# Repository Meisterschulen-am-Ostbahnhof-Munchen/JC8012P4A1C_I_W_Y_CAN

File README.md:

# JC8012P4A1C Enclosure & CAN Addon System

Enclosure, mounting and CAN/Power addon board for the Guition JC8012P4A1C (ESP32-P4, 10.1")
display, used by [espVT](https://github.com/Meisterschulen-am-Ostbahnhof-Munchen/espVT).

The system integrates an ISOBUS/CAN interface, 12 V power supply, a 3D-printed enclosure frame,
and an FR4 backplate with VESA 100 mount and speaker. An optional second variant extends the unit
with a 12-key tactile keypad next to the display.

**Online:** interactive BOMs, schematics and drawings at
<https://meisterschulen-am-ostbahnhof-munchen.github.io/JC8012P4A1C_I_W_Y_CAN/>

More renderings and how they are made: [assembly/render/](assembly/render/README.md).

## Repository Structure

The project is structured into PCBs, mechanics and final assembly:

```text
JC8012P4A1C_I_W_Y_CAN/
├── pcbs/
│   ├── can_power/        # CAN-Bus & 12V/5V power supply addon board
│   ├── backplate/        # FR4 backplate with VESA 100 mount & speaker grille (variant 1)
│   ├── backplate_keypad/ # Widened FR4 backplate for variant 2 (with keypad)
│   ├── keypad/           # 12-key tactile keypad PCB (variant 2)
│   ├── keypad_2b/        # keypad with dimmable WL-ICLED backlight (variant 2b)
│   └── can_power_2b/     # CAN board with J4 for the keypad LEDs (variant 2b)
├── mechanics/            # 3D printed frame designs (FreeCAD scripts, STL & STEP files)
├── assembly/             # Assembly drawings (A3 PDF), 3D render models & assembly scripts
├── assembly_bom.csv      # Complete mechanical parts, fasteners & cables BOM
├── mouser_order.csv      # Ordering list for non-Würth components
└── README.md
```

## Variants

| Component | Variant 1 (Standard) | Variant 2 (with Keypad) | Variant 2b (backlit keypad) |
|---|---|---|---|
| Display | Guition JC8012P4A1C (10.1" ESP32-P4) | Guition JC8012P4A1C (10.1" ESP32-P4) | as variant 2 |
| CAN / Power Board | [`pcbs/can_power/`](pcbs/can_power/README.md) | [`pcbs/can_power/`](pcbs/can_power/README.md) | [`pcbs/can_power_2b/`](pcbs/can_power_2b/README.md) (with J4 for the LEDs) |
| Frame | `mechanics/frame.stl` | `mechanics/frame_keypad.stl` | as variant 2 |
| Backplate | [`pcbs/backplate/`](pcbs/backplate/README.md) | [`pcbs/backplate_keypad/`](pcbs/backplate_keypad/README.md) (296.9 mm wide) | as variant 2 |
| Keypad | — | [`pcbs/keypad/`](pcbs/keypad/README.md) (12 tactile keys F1–F12) | [`pcbs/keypad_2b/`](pcbs/keypad_2b/README.md) (WL-ICLED windows + background, dimmable) |
| Assembly Drawing | [assembly/JC8012P4A1C_assembly_variant1.pdf](assembly/JC8012P4A1C_assembly_variant1.pdf) | [assembly/JC8012P4A1C_assembly_variant2_keypad.pdf](assembly/JC8012P4A1C_assembly_variant2_keypad.pdf) | as variant 2, plus the 3 wire LED cable |

Details on mechanics: [mechanics/README.md](mechanics/README.md).  
Details on assembly: [assembly/README.md](assembly/README.md).

## Bills of Materials (BOM)

| BOM | File |
|---|---|
| CAN & Power board | [pcbs/can_power/production/JC8012P4A1C_I_W_Y_CAN_bom.csv](pcbs/can_power/production/JC8012P4A1C_I_W_Y_CAN_bom.csv) |
| Back plate (variant 1) | [pcbs/backplate/production/JC8012P4A1C_backplate_bom.csv](pcbs/backplate/production/JC8012P4A1C_backplate_bom.csv) |
| Back plate (variant 2, keypad) | [pcbs/backplate_keypad/production/JC8012P4A1C_backplate_keypad_bom.csv](pcbs/backplate_keypad/production/JC8012P4A1C_backplate_keypad_bom.csv) |
| Keypad (variant 2) | [pcbs/keypad/production/JC8012P4A1C_keypad_bom.csv](pcbs/keypad/production/JC8012P4A1C_keypad_bom.csv) |
| Keypad (variant 2b, backlit) | [pcbs/keypad_2b/production/JC8012P4A1C_keypad_2b_bom.csv](pcbs/keypad_2b/production/JC8012P4A1C_keypad_2b_bom.csv) |
| CAN & Power board (variant 2b) | [pcbs/can_power_2b/production/JC8012P4A1C_I_W_Y_CAN_2b_bom.csv](pcbs/can_power_2b/production/JC8012P4A1C_I_W_Y_CAN_2b_bom.csv) |
| Final assembly (mechanical fasteners, cables) | [assembly_bom.csv](assembly_bom.csv) |
| Parts to order at Mouser (all non-Würth parts) | [mouser_order.csv](mouser_order.csv) |

### Interactive HTML BOMs (Assembly Checklists)

For manual assembly, interactive HTML BOMs (with checkboxes for soldering and inspection) are provided:

| Board | Interactive BOM |
|---|---|
| CAN & Power board | [pcbs/can_power/production/JC8012P4A1C_I_W_Y_CAN_ibom.html](pcbs/can_power/production/JC8012P4A1C_I_W_Y_CAN_ibom.html) |
| Back plate | [pcbs/backplate/production/JC8012P4A1C_backplate_ibom.html](pcbs/backplate/production/JC8012P4A1C_backplate_ibom.html) |
| Back plate (keypad variant) | [pcbs/backplate_keypad/production/JC8012P4A1C_backplate_keypad_ibom.html](pcbs/backplate_keypad/production/JC8012P4A1C_backplate_keypad_ibom.html) |
| Keypad | [pcbs/keypad/production/JC8012P4A1C_keypad_ibom.html](pcbs/keypad/production/JC8012P4A1C_keypad_ibom.html) |
| Keypad 2b | [pcbs/keypad_2b/production/JC8012P4A1C_keypad_2b_ibom.html](pcbs/keypad_2b/production/JC8012P4A1C_keypad_2b_ibom.html) |
| CAN & Power board 2b | [pcbs/can_power_2b/production/JC8012P4A1C_I_W_Y_CAN_2b_ibom.html](pcbs/can_power_2b/production/JC8012P4A1C_I_W_Y_CAN_2b_ibom.html) |

## Manufacturing

Each PCB folder in `pcbs/` contains its complete KiCad 10 project, local component libraries (`lib/`), documentation (`docs/`), and fabrication outputs (`production/`).
See the respective README files in [`pcbs/can_power/`](pcbs/can_power/README.md), [`pcbs/backplate/`](pcbs/backplate/README.md), [`pcbs/backplate_keypad/`](pcbs/backplate_keypad/README.md), and [`pcbs/keypad/`](pcbs/keypad/README.md) for generation commands and specifications.

The 3D-printable frame is generated using FreeCAD scripts in [`mechanics/`](mechanics/README.md).

## Licence

- Schematics, PCB layouts, scripts and documentation: GPL-3.0 ([LICENSE](LICENSE)).
- `pcbs/*/lib/` and `assembly/models/`: symbols, footprints and 3D models from the Würth Elektronik eiSos libraries, licensed CC BY-SA 4.0 with the Würth exception for designs that use them (see `Wurth_Disclaimer_READ_ME.txt` in these folders).
- Footprints and 3D models from the KiCad standard libraries: CC BY-SA 4.0 with the KiCad exception.
- `mechanics/`: derivative of a Thingiverse design by 8bitmcu, CC BY-SA, see [mechanics/LICENSE.md](mechanics/LICENSE.md).

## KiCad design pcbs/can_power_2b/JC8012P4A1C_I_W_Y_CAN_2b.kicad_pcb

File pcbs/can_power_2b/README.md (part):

# JC8012P4A1C CAN & Power Board, variant 2b

The CAN board of `../can_power` with one addition for the backlit keypad
`../keypad_2b`: **J4** brings 5 V, GND and the LED data (GPIO2) to the keypad.
Everything else is unchanged.

ISOBUS / CAN interface (250 kbit/s) for the Guition JC8012P4A1C (ESP32-P4, 10.1")
display, used by [espVT](https://github.com/Meisterschulen-am-Ostbahnhof-Munchen/espVT).
The board is mounted on the back of the display board and powered from the 12 V
board net. It also supplies 5 V to the display board.

KiCad 10 project. Project-local libraries are in `lib/`.

Top view: [docs/board_3d_top.png](docs/board_3d_top.png)

## Connections

| Connector | Part | Purpose |
|---|---|---|
| J1 | Würth WR-PHD 610110249121 (2×5 pin header, SMT, right angled) | ribbon cable to IDC D-Sub 9 female Würth 618009221923 |
| J2 | Würth WR-FPC 68711414522 (14 pin, 0.5 mm) | FFC to FPC3 "EXTEND1" of the display board |
| J3 | Würth WR-WTB 653104131822 (4 pin, 1.25 mm) | 5 V to CN2 of the display board |
| J4 | Würth WR-WTB 653103131822 (3 pin, 1.25 mm) | 5 V, GND and LED data to J2 of the keypad 2b |

### D-Sub 9 (via ribbon cable on J1)

Pinout of the Müller-Elektronik BASIC-Terminal CAN-ISO connector. It fits the
adapter cable 481595 (D-Sub 9 male to In-Cab CPC-9 female).

| D-Sub | J1 | Signal |
|---|---|---|
| 1 | 1 | CAN_L |
| 2 | 3 | CAN_L |
| 3 | 5 | TBC_GND (see R8) |
| 4 | 7 | CAN_H |
| 5 | 9 | TBC_PWR_in (not used) |
| 6 | 2 | ECU_GND |
| 7 | 4 | CAN_H |
| 8 | 6 | TBC_PWR_out |
| 9 | 8 | ECU_PWR (12 V board net) |
| – | 10 | not used |

CAN_L (1/2) and CAN_H (4/7) are connected on the board to loop the bus through.

**Pin numbering:** J1 is numbered like the IDC socket 61201023021: pin 1 and
all odd pins are in the upper row (away from the PCB, pin tips away from the
body of J1), the even pins in the lower row. Pin 1 is at the end next to R8
(silkscreen line next to the pad). The Würth datasheet of 610110249121 numbers
the two rows the other way round (pin 1 in the lower row); with that numbering
every position of the IDC socket meets the neighbour pin of the other row
(1↔2, 3↔4, ...). The footprint therefore deviates from the datasheet on
purpose (since Rev B).

**Polarisation:** J1 has no shroud (an 8 mm high part is the maximum under
the cover, a box header with IDC socket would be too high). To prevent the
IDC socket from being plugged in turned by 180°, cut off pin 10 of J1 (lower
row, end away from R8, marked "cut" on the silkscreen) and close position 10
of the IDC socket with a coding plug. Pins 9 and 10 are not used. Plugged in
turned, ECU_PWR (12 V) would end up on CAN_L and the board GND would stay
open.

## Mechanics

- All parts on the top side (SMT only), nothing on the bottom side
- Stack height: cover 14 mm − display board 1.5 mm − M2 standoffs 3 mm −
  addon board 1.5 mm ≈ 8 mm free above the addon board
- Fixing on the 58 × 46 mm grid of the display board standoffs S1–S4
  (H1 = S1, H2 = S4, H3 = S2, H4 = S3): SMD steel spacers Würth WA-SMST
  9774025943R (L 2.5 mm, through hole 2.25 mm), land pattern from the
  datasheet, but the GND pad on top is a copper ring 3.5-5.3 mm: 0.25 mm without
  copper around the 3.0 mm **non-plated** hole for the Ø 2.8 × 1.4 mm collar of
  the spacer, so the hole is clearly unplated in the JLC order.
- Screws **M2×6**, without washer: spacer 2.5 mm + PCB 1.6 mm leaves 1.9 mm
  thread engagement in the 2.5 mm deep blind thread of S1–S4. M2×8 would
  bottom out.
- Notches for CN5 (pin header), the 100 µF capacitor next to S4 and the
  CR1220 RTC holder of the display board

### FPC3 (J2)

| Pin | Signal |
|---|---|
| 1, 2 | GND |
| 7 | CAN_RXD (GPIO5) |
| 8 | CAN_TXD (GPIO4) |
| 9 | CAN_NEN (GPIO3, 10k pull-down: transceiver active by default) |
| 10 | LED_DATA (GPIO2) -> R11 33 R -> J4 pin 3 |
| 13, 14 | +3V3 (VDDA, transceiver VIO) |

FFC: 14 pin, 0.5 mm pitch, **type B (contacts on opposite sides)**.
The cable leaves FPC3 towards the board edge, makes one 180° turn and enters
J2 from the edge of the addon board. Both connectors are bottom-contact ZIF
with the same orientation (opening towards the edge, pin 1 on the right
side seen from the back of the display, next to the TF card), so pin 1
connects to pin 1. A type A cable would have its contacts facing up at J2;
turning it over to make it fit reverses the pin order and swaps GND (1/2)
and 3V3 (13/14).

## Keypad backlight (J4)

| J4 | Signal |
|---|---|
| 1 | +5V (In2 plane) |
| 2 | GND |
| 3 | LED data: GPIO2 (FPC3 pin 10) through R11 33 R |

J4 sits at the bottom notch of the board, the opening points into the notch.
GPIO2 is in the 3.3 V domain (VDDPST_1). GPIO45-48 on FPC3 were not used: they are
supplied from ESP_LDO_VO4 like the SD card and can be switched to 1.8 V.
The level shifter to 5 V is on the keypad. Six GND stitching vias under J4 / R11
were removed, the board text was moved up and reads "Rev 2b".

## Termination

ISO 11783-2 ECU Type I WEAK: split termination 750 Ω + 750 Ω with 47 nF to GND.

## TBC power output and R8

Like the BASIC-Terminal, the board supplies power for the terminating bias
circuits (TBC) on D-Sub pin 8 (TBC_PWR_out): board net minus about 0.4 V
(Schottky diode D4), limited by PTC F2 (0.14 A). Some harnesses do not start
without it.

**R8 (0 Ω, TBC_GND to GND) is not fitted (DNP) by default.** This keeps
TBC_GND isolated, which is the compatible default. If a harness needs a
TBC_GND return for its terminator, fit R8 with a 0 Ω resistor (0603).

## Power

- 12 V board net only (ECU_PWR), fuse F1 1 A slow
- Bidirectional TVS Würth 824551241 (SMDJ24CA), clamping ≤ 38.9 V
- Reverse polarity protection: dual P-MOSFET Vishay Si4948BEY (SO-8), both
  halves in parallel, 15 V gate zener. Drop-in for the KiCad symbol
  DMP6050SSD (same SO-8 pinout S1 G1 S2 G2 D2 D2 D1 D1), which is used as
  the schematic symbol.
- Buck converter Würth MagI³C 171030601: 5 V / 3 A for the transceiver and the display board

## Test points

SMD pads (1.5 mm), labelled with the net name on the silkscreen:

| TP | Net | Position |
|---|---|---|
| TP1 | +5V | next to J3 |
| TP2 | GND | next to J3 |
| TP3 | CAN_H | between D1 and J1 |
| TP4 | CAN_L | between D1 and J1 |
| TP5 | VIN_PROT (12 V after fuse and reverse polarity protection) | right of C13, below L2 |

## PCB

66 × 54 mm, 1.6 mm, 6 layers:

| Layer | Use |
|---|---|
| F.Cu | all parts and signals, GND pour, local pours for VIN_PROT, VIN_BUCK and +5V |
| In1.Cu | GND plane |
| In2.Cu | +5V plane |
| In3.Cu | GND plane (also balances the copper of In2) |
| In4.Cu | GND plane |
| B.Cu | GND plane, one short signal (CAN_NEN) |

- Vias 0.5 mm / 0.3 mm drill (a 0.2 mm drill costs extra at JLCPCB). Many vias are placed in SMD pads (GND and
  +5V pads, 77 thermal vias under the exposed pad of U2), so the vias
  **must be epoxy filled and capped** (via-in-pad). Without this, solder
  is drawn into the holes during reflow.
- GND stitching vias on a 4 mm grid connect all GND layers.
- Pours connect solid to SMD pads and to the spacer pads H1–H4 (reflow
  soldering, a hand soldering iron will not heat them).
- Net classes: Power 0.8 mm (12 V path and +5V), CAN 0.3 mm, Default 0.25 mm.

## Manufacturing

The current Gerber and drill files are in the zip
`production/JC8012P4A1C_I_W_Y_CAN_2b_gerber.zip` (ready for upload), the BOM
in `production/JC8012P4A1C_I_W_Y_CAN_2b_bom.csv`. Make them again after changes
to the board: in KiCad PCB editor → File → Fabrication Outputs → Gerbers and
Drill Files, or from the command line:

```sh
kicad-cli pcb export gerbers -o production/gerber -l F.Cu,In1.Cu,In2.Cu,In3.Cu,In4.Cu,B.Cu,F.Paste,B.Paste,F.Silkscreen,B.Silkscreen,F.Mask,B.Mask,Edge.Cuts --subtract-soldermask --no-x2 --no-netlist --check-zones JC8012P4A1C_I_W_Y_CAN_2b.kicad_pcb
kicad-cli pcb export drill -o production/gerber/ --format excellon --excellon-units mm --excellon-separate-th JC8012P4A1C_I_W_Y_CAN_2b.kicad_pcb
```

Zip the content of `production/gerber` (the folder itself is not in the
repository) to `production/JC8012P4A1C_I_W_Y_CAN_2b_gerber.zip` and upload it (e.g. JLCPCB:
6 layers, 1.6 mm, via covering "Epoxy Filled & Capped").

Interactive HTML BOM:

```sh
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
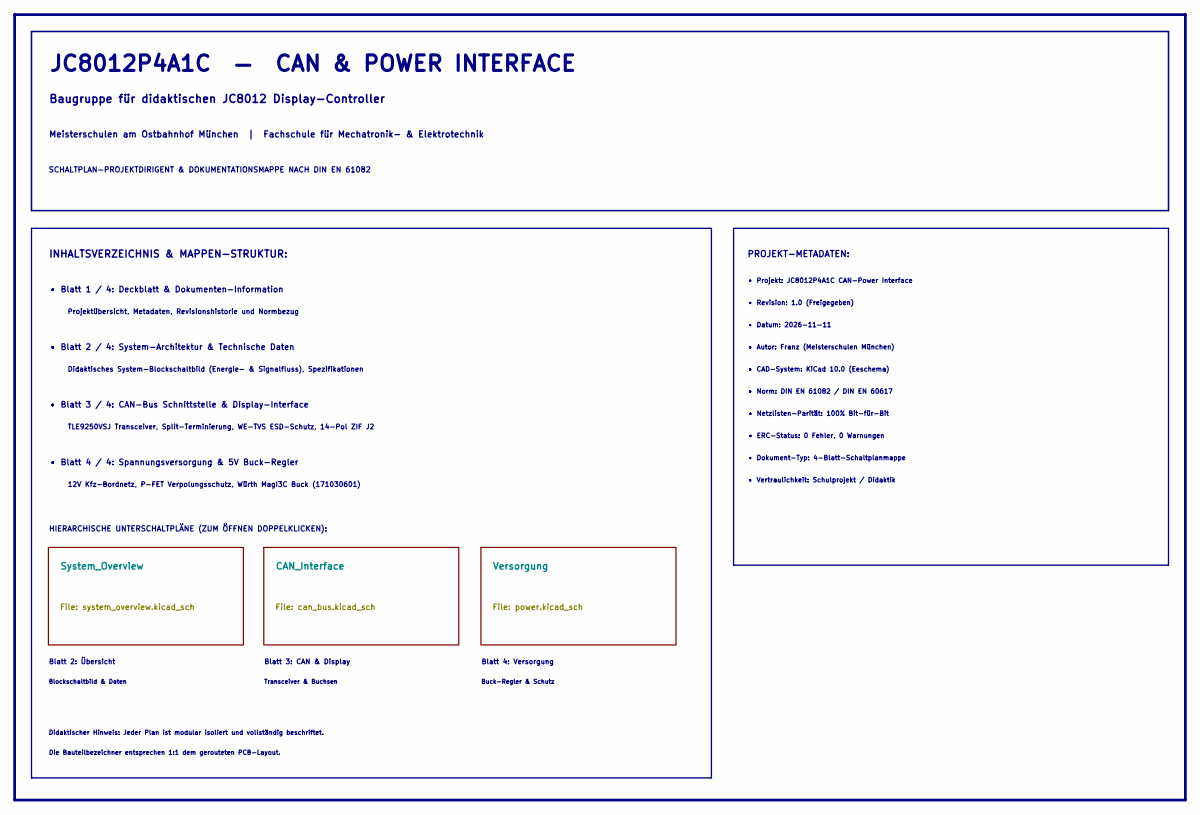
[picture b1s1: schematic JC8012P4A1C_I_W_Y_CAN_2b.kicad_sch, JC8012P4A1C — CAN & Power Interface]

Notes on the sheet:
Projektübersicht, Metadaten, Revisionshistorie und Normbezug
12V Kfz-Bordnetz, P-FET Verpolungsschutz, Würth MagI3C Buck (171030601)
Blatt 2: Übersicht
• CAD-System: KiCad 10.0 (Eeschema)
• Revision: 1.0 (Freigegeben)
HIERARCHISCHE UNTERSCHALTPLÄNE (ZUM ÖFFNEN DOPPELKLICKEN):
Didaktisches System-Blockschaltbild (Energie- & Signalfluss), Spezifikationen
• Netzlisten-Parität: 100% Bit-für-Bit
PROJEKT-METADATEN:
Meisterschulen am Ostbahnhof München | Fachschule für Mechatronik- & Elektrotechnik
• Norm: DIN EN 61082 / DIN EN 60617
• Blatt 3 / 4: CAN-Bus Schnittstelle & Display-Interface
Baugruppe für didaktischen JC8012 Display-Controller
• Dokument-Typ: 4-Blatt-Schaltplanmappe
• ERC-Status: 0 Fehler, 0 Warnungen
Blatt 4: Versorgung
INHALTSVERZEICHNIS & MAPPEN-STRUKTUR:
• Blatt 4 / 4: Spannungsversorgung & 5V Buck-Regler
Buck-Regler & Schutz
• Blatt 2 / 4: System-Architektur & Technische Daten
Blatt 3: CAN & Display
Blockschaltbild & Daten
SCHALTPLAN-PROJEKTDIRIGENT & DOKUMENTATIONSMAPPE NACH DIN EN 61082
• Datum: 2026-11-11
• Vertraulichkeit: Schulprojekt / Didaktik
JC8012P4A1C — CAN & POWER INTERFACE
• Blatt 1 / 4: Deckblatt & Dokumenten-Information
Die Bauteilbezeichner entsprechen 1:1 dem gerouteten PCB-Layout.
Transceiver & Buchsen
TLE9250VSJ Transceiver, Split-Terminierung, WE-TVS ESD-Schutz, 14-Pol ZIF J2
Didaktischer Hinweis: Jeder Plan ist modular isoliert und vollständig beschriftet.
• Autor: Franz (Meisterschulen München)
• Projekt: JC8012P4A1C CAN-Power Interface

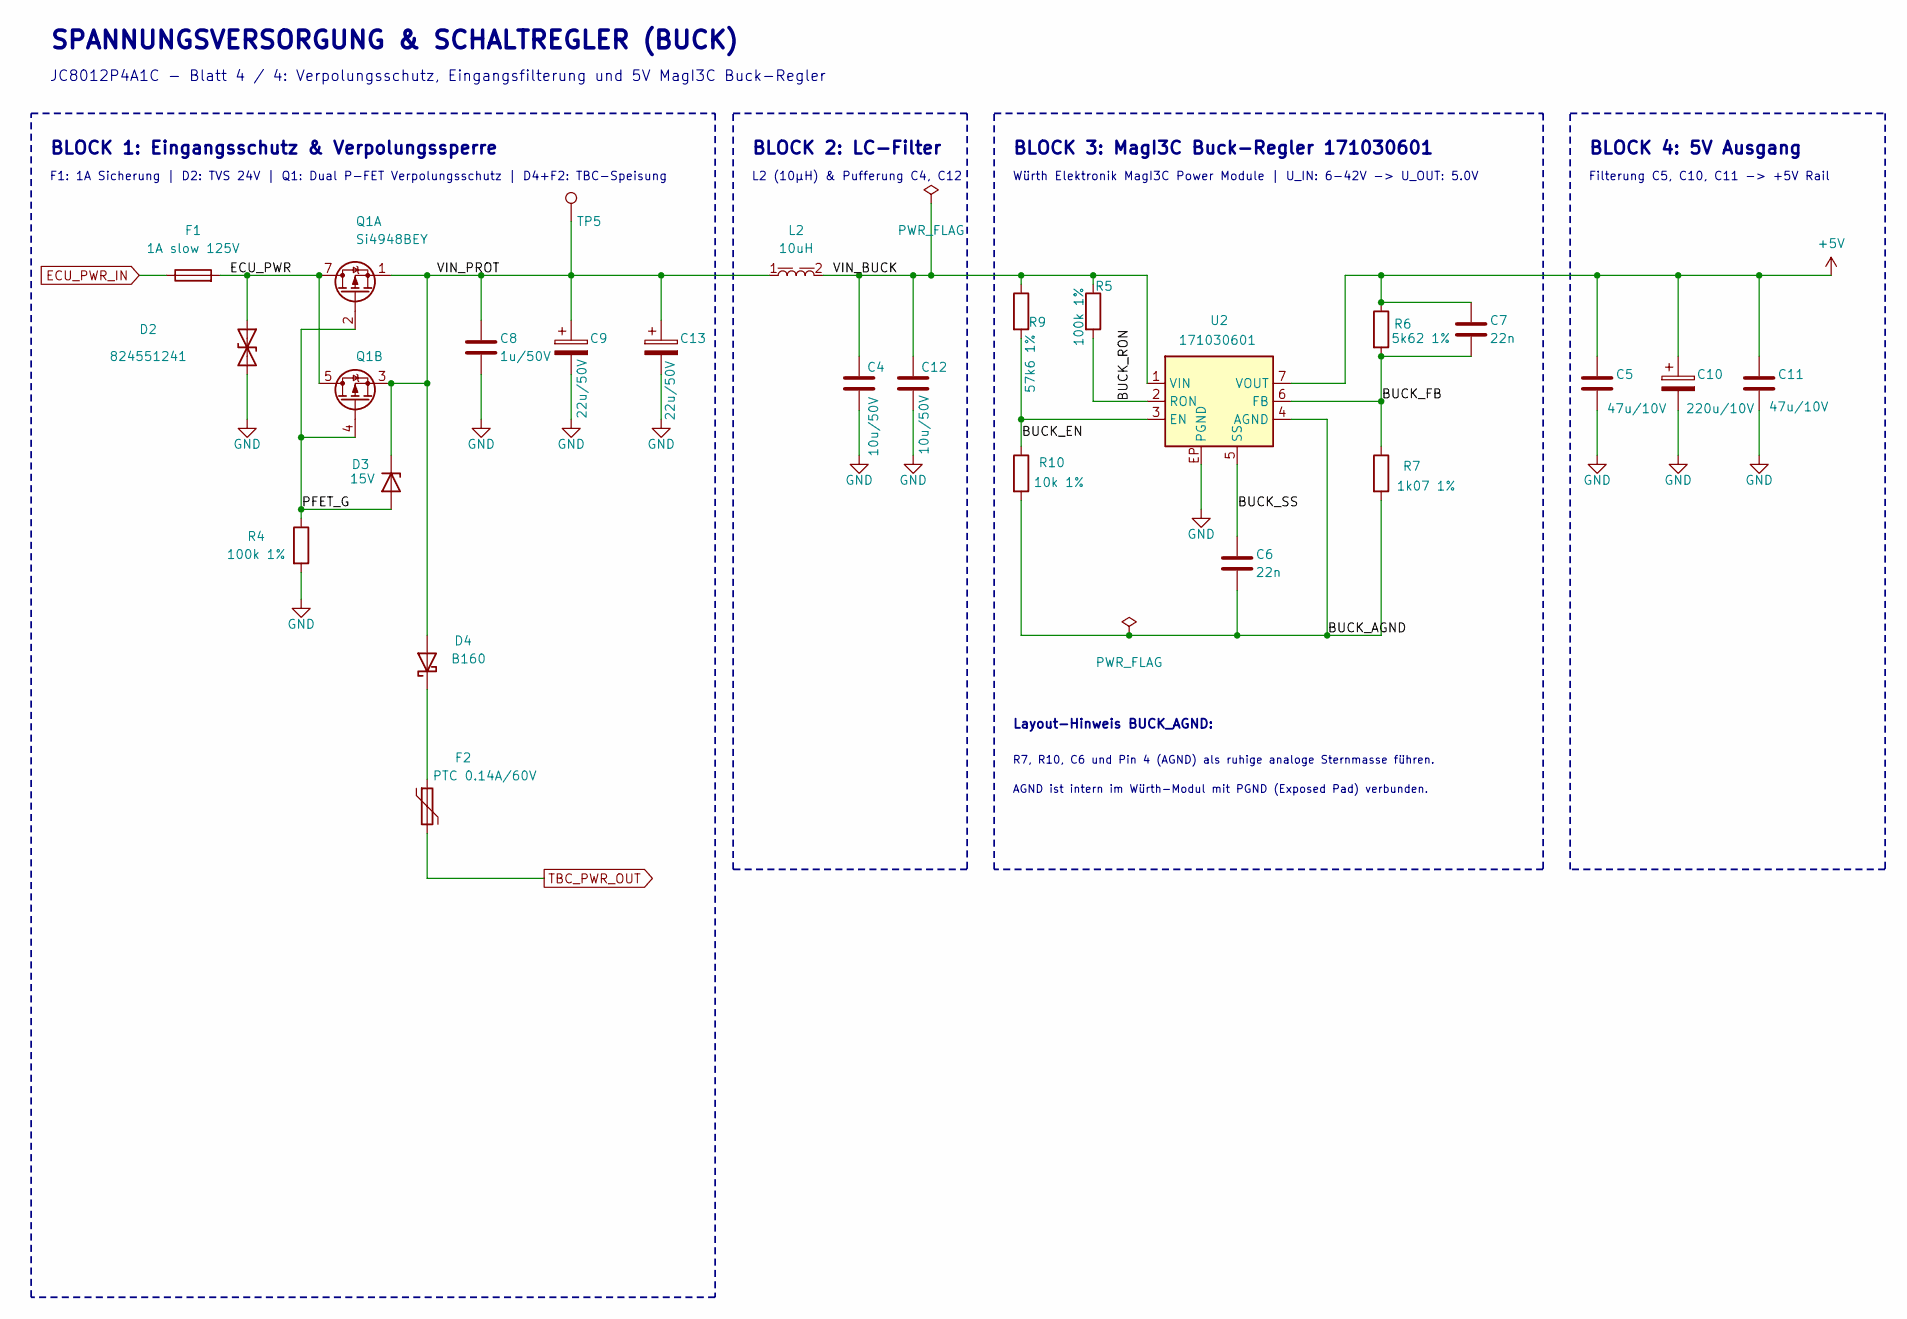
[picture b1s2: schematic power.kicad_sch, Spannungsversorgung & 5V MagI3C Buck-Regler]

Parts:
C4, C12: 10u/50V; C_1210_3225Metric; MPN 885012209073
C5, C11: 47u/10V; C_1210_3225Metric; MPN 885012109007
C6, C7: 22n; C_0603_1608Metric; MPN 885012206091
C8: 1u/50V; C_1210_3225Metric; MPN 885012209047
C9, C13: 22u/50V; CP_Wurth_WCAP-ASLI-D6.3L5.5; MPN 865080643008
C10: 220u/10V; CP_Wurth_WCAP-PSLP-D6.3L5.8; MPN 875105244013
D2: 824551241; D_Wurth_WE-TVSP-DO214-AB-3000W_BI; MPN 824551241
D3: 15V; D_SOD-123; MPN MMSZ5245B_R1_00001
D4: B160; D_SMA; MPN B160-13-F
F1: 1A slow 125V; Fuse_Littelfuse-NANO2-451_453; MPN 0452001.MRL
F2: PTC 0.14A/60V; Fuse_1812_4532Metric; MPN MF-MSMF014-2
L2: 10uH; L_Wurth_WE-PD2-5848; MPN 74477410
Q1: Si4948BEY; SOIC-8_3.9x4.9mm_P1.27mm; MPN SI4948BEY-T1-E3
R4, R5: 100k 1%; R_0603_1608Metric; MPN RC0603FR-07100KL
R6: 5k62 1%; R_0603_1608Metric; MPN RC0603FR-075K62L
R7: 1k07 1%; R_0603_1608Metric; MPN RC0603FR-071K07L
R9: 57k6 1%; R_0603_1608Metric; MPN RC0603FR-0757K6L
R10: 10k 1%; R_0603_1608Metric; MPN RC0603FR-0710KL
TP5: VIN_PROT; TestPoint_Pad_D1.5mm
U2: 171030601; U_Wurth_WPME-VDRM-TO263-7EP; MPN 171030601

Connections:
+5V: C5.1, C7.1, C10.1, C11.1, R6.1, U2.7 (VOUT); also elsewhere on the board
/Versorgung/BUCK_AGND: C6.2, R7.2, R10.2, U2.4 (AGND)
/Versorgung/BUCK_EN: R9.2, R10.1, U2.3 (EN)
/Versorgung/BUCK_FB: C7.2, R6.2, R7.1, U2.6 (FB)
/Versorgung/BUCK_RON: R5.2, U2.2 (RON)
/Versorgung/BUCK_SS: C6.1, U2.5 (SS)
/Versorgung/ECU_PWR: D2.1 (A1), F1.2, Q1.5 (D2), Q1.6 (D2), Q1.7 (D1), Q1.8 (D1)
/Versorgung/PFET_G: D3.2 (A), Q1.2 (G1), Q1.4 (G2), R4.1
/Versorgung/VIN_BUCK: C4.1, C12.1, L2.2, R5.1, R9.1, U2.1 (VIN)
/Versorgung/VIN_PROT: C8.1, C9.1, C13.1, D3.1 (K), D4.2 (A), L2.1, Q1.1 (S1), Q1.3 (S2), TP5.1 (1_1)
unnamed: D4.1 (K), F2.1
TBC_PWR_OUT: F2.2; also elsewhere on the board

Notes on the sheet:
Würth Elektronik MagI3C Power Module | U_IN: 6-42V -> U_OUT: 5.0V
JC8012P4A1C - Blatt 4 / 4: Verpolungsschutz, Eingangsfilterung und 5V MagI3C Buck-Regler
R7, R10, C6 und Pin 4 (AGND) als ruhige analoge Sternmasse führen.
BLOCK 3: MagI3C Buck-Regler 171030601
BLOCK 4: 5V Ausgang
Layout-Hinweis BUCK_AGND:
AGND ist intern im Würth-Modul mit PGND (Exposed Pad) verbunden.
F1: 1A Sicherung | D2: TVS 24V | Q1: Dual P-FET Verpolungsschutz | D4+F2: TBC-Speisung
BLOCK 1: Eingangsschutz & Verpolungssperre
L2 (10µH) & Pufferung C4, C12
Filterung C5, C10, C11 -> +5V Rail
SPANNUNGSVERSORGUNG & SCHALTREGLER (BUCK)
BLOCK 2: LC-Filter

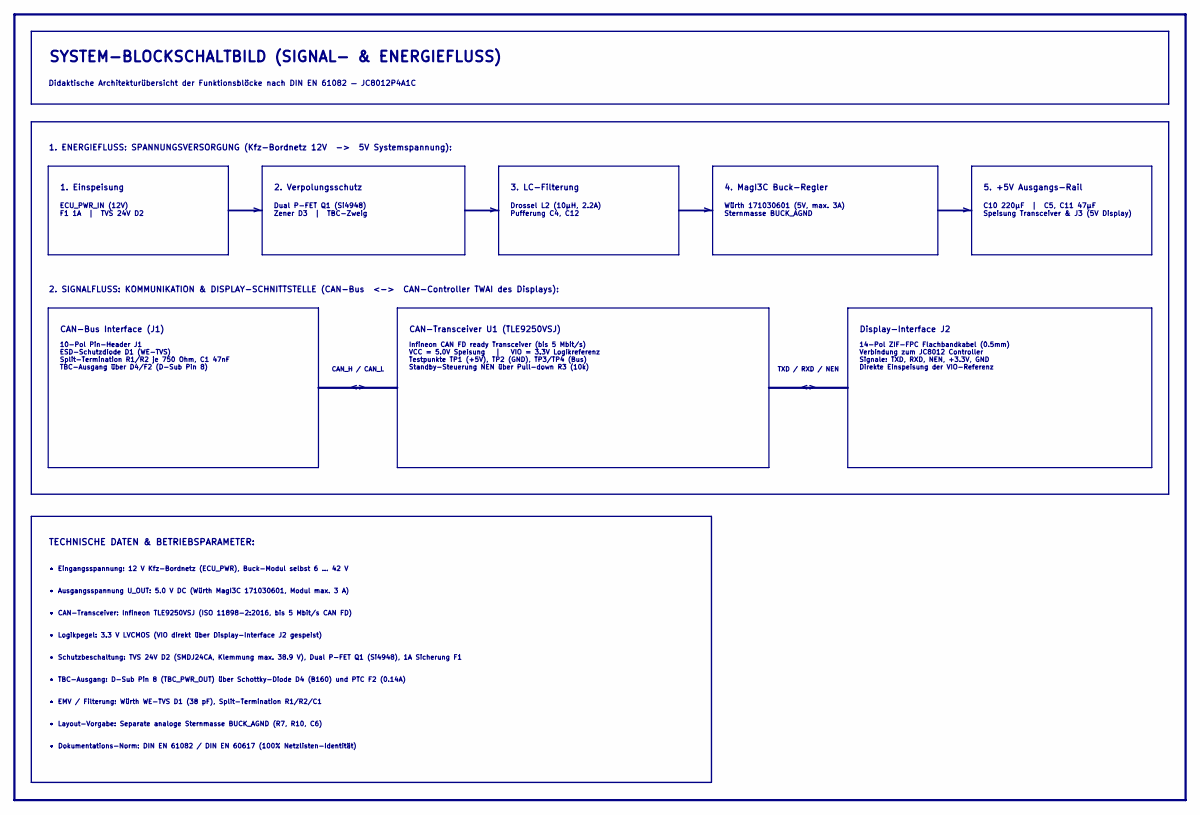
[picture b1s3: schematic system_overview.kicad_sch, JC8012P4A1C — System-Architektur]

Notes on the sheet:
1. Einspeisung
5. +5V Ausgangs-Rail
• Schutzbeschaltung: TVS 24V D2 (SMDJ24CA, Klemmung max. 38.9 V), Dual P-FET Q1 (Si4948), 1A Sicherung F1
TECHNISCHE DATEN & BETRIEBSPARAMETER:
CAN_H / CAN_L
Würth 171030601 (5V, max. 3A) Sternmasse BUCK_AGND
• EMV / Filterung: Würth WE-TVS D1 (38 pF), Split-Termination R1/R2/C1
• Layout-Vorgabe: Separate analoge Sternmasse BUCK_AGND (R7, R10, C6)
• CAN-Transceiver: Infineon TLE9250VSJ (ISO 11898-2:2016, bis 5 Mbit/s CAN FD)
Drossel L2 (10µH, 2.2A) Pufferung C4, C12
Infineon CAN FD ready Transceiver (bis 5 Mbit/s) VCC = 5.0V Speisung | VIO = 3.3V Logikreferenz Testpunkte TP1 (+5V), TP2 (GND), TP3/TP4 (Bus) Standby-Steuerung NEN über Pull-down R3 (10k)
CAN-Transceiver U1 (TLE9250VSJ)
Dual P-FET Q1 (Si4948) Zener D3 | TBC-Zweig
Didaktische Architekturübersicht der Funktionsblöcke nach DIN EN 61082 — JC8012P4A1C
1. ENERGIEFLUSS: SPANNUNGSVERSORGUNG (Kfz-Bordnetz 12V -> 5V Systemspannung):
4. MagI3C Buck-Regler
14-Pol ZIF-FPC Flachbandkabel (0.5mm) Verbindung zum JC8012 Controller Signale: TXD, RXD, NEN, +3.3V, GND Direkte Einspeisung der VIO-Referenz
TXD / RXD / NEN
2. SIGNALFLUSS: KOMMUNIKATION & DISPLAY-SCHNITTSTELLE (CAN-Bus <-> CAN-Controller TWAI des Displays):
3. LC-Filterung
C10 220µF | C5, C11 47µF Speisung Transceiver & J3 (5V Display)
• TBC-Ausgang: D-Sub Pin 8 (TBC_PWR_OUT) über Schottky-Diode D4 (B160) und PTC F2 (0.14A)
• Dokumentations-Norm: DIN EN 61082 / DIN EN 60617 (100% Netzlisten-Identität)
• Logikpegel: 3.3 V LVCMOS (VIO direkt über Display-Interface J2 gespeist)
Display-Interface J2
2. Verpolungsschutz
CAN-Bus Interface (J1)
• Ausgangsspannung U_OUT: 5.0 V DC (Würth MagI3C 171030601, Modul max. 3 A)
ECU_PWR_IN (12V) F1 1A | TVS 24V D2
10-Pol Pin-Header J1 ESD-Schutzdiode D1 (WE-TVS) Split-Termination R1/R2 je 750 Ohm, C1 47nF TBC-Ausgang über D4/F2 (D-Sub Pin 8)
• Eingangsspannung: 12 V Kfz-Bordnetz (ECU_PWR), Buck-Modul selbst 6 ... 42 V
SYSTEM-BLOCKSCHALTBILD (SIGNAL- & ENERGIEFLUSS)

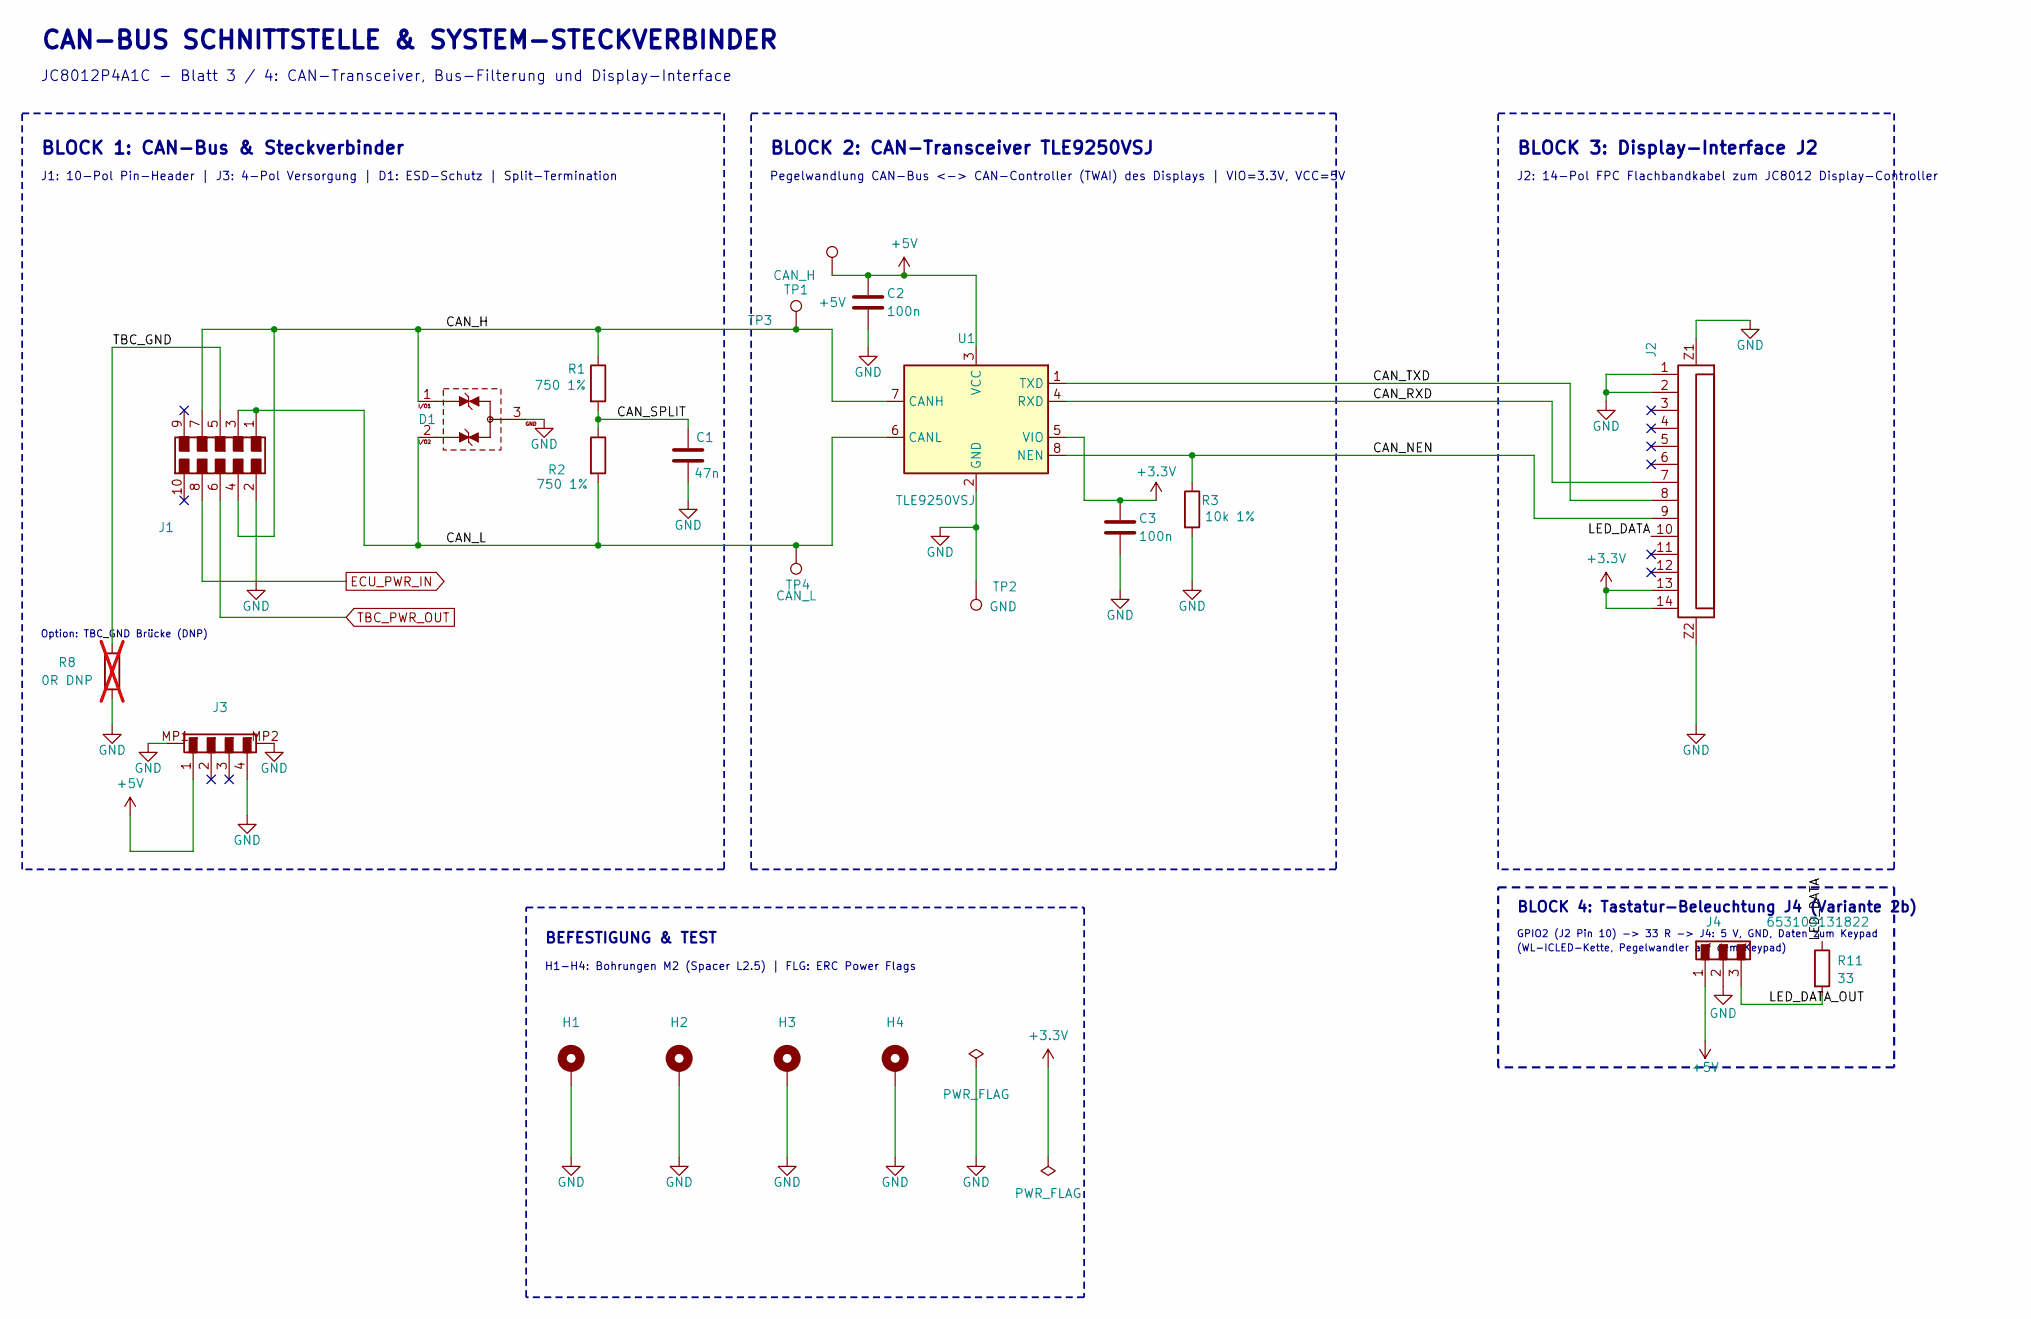
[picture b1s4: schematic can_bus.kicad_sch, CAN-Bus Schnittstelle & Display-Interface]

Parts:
C1: 47n; C_0603_1608Metric; MPN 885012206093
C2, C3: 100n; C_0603_1608Metric; MPN 885012206095
D1: 824094024; D_Wurth_WE-TVS-SOT23-3L; MPN 824094024
H1, H2, H3, H4: Spacer M2 L2.5; A_Wurth_WA-SMST_9774025943R; MPN 9774025943R
J1: 610110249121; J_Wurth_WR-PHD_610110249121; MPN 610110249121
J2: 68711414522; J_Wurth_WR-FPC_68711414522; MPN 68711414522
J3: 653104131822; J_Wurth_WR-WTB_653104131822; MPN 653104131822
J4: 653103131822; J_Wurth_WR-WTB_653103131822; MPN 653103131822
R1, R2: 750 1%; R_1206_3216Metric; MPN RC1206FR-07750RL
R3: 10k 1%; R_0603_1608Metric; MPN RC0603FR-0710KL
R8: 0R DNP; R_0603_1608Metric; MPN RC0603JR-070RL; not fitted
R11: 33; R_0603_1608Metric; MPN RC0603FR-0733RL
TP1: +5V; TestPoint_Pad_D1.5mm
TP2: GND; TestPoint_Pad_D1.5mm
TP3: CAN_H; TestPoint_Pad_D1.5mm
TP4: CAN_L; TestPoint_Pad_D1.5mm
U1: TLE9250VSJ; SOIC-8_3.9x4.9mm_P1.27mm; MPN TLE9250VSJXUMA1

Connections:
+3.3V: C3.1, J2.13, J2.14, U1.5 (VIO)
+5V: C2.1, J3.1, J4.1, TP1.1 (1_1), U1.3 (VCC); also elsewhere on the board
/CAN_Interface/CAN_H: D1.1 (I/O1), J1.4, J1.7, R1.1, TP3.1 (1_1), U1.7 (CANH)
/CAN_Interface/CAN_L: D1.2 (I/O2), J1.1, J1.3, R2.2, TP4.1 (1_1), U1.6 (CANL)
/CAN_Interface/CAN_NEN: J2.9, R3.1, U1.8 (NEN)
/CAN_Interface/CAN_RXD: J2.7, U1.4 (RXD)
/CAN_Interface/CAN_SPLIT: C1.1, R1.2, R2.1
/CAN_Interface/CAN_TXD: J2.8, U1.1 (TXD)
/CAN_Interface/LED_DATA: J2.10, R11.1
/CAN_Interface/LED_DATA_OUT: J4.3, R11.2
/CAN_Interface/TBC_GND: J1.5, R8.1
TBC_PWR_OUT: J1.6; also elsewhere on the board

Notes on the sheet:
Pegelwandlung CAN-Bus <-> CAN-Controller (TWAI) des Displays | VIO=3.3V, VCC=5V
JC8012P4A1C - Blatt 3 / 4: CAN-Transceiver, Bus-Filterung und Display-Interface
H1-H4: Bohrungen M2 (Spacer L2.5) | FLG: ERC Power Flags
BEFESTIGUNG & TEST
BLOCK 1: CAN-Bus & Steckverbinder
BLOCK 2: CAN-Transceiver TLE9250VSJ
J2: 14-Pol FPC Flachbandkabel zum JC8012 Display-Controller
BLOCK 3: Display-Interface J2
Option: TBC_GND Brücke (DNP)
CAN-BUS SCHNITTSTELLE & SYSTEM-STECKVERBINDER
J1: 10-Pol Pin-Header | J3: 4-Pol Versorgung | D1: ESD-Schutz | Split-Termination
BLOCK 4: Tastatur-Beleuchtung J4 (Variante 2b)
GPIO2 (J2 Pin 10) -> 33 R -> J4: 5 V, GND, Daten zum Keypad
(WL-ICLED-Kette, Pegelwandler auf dem Keypad)

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
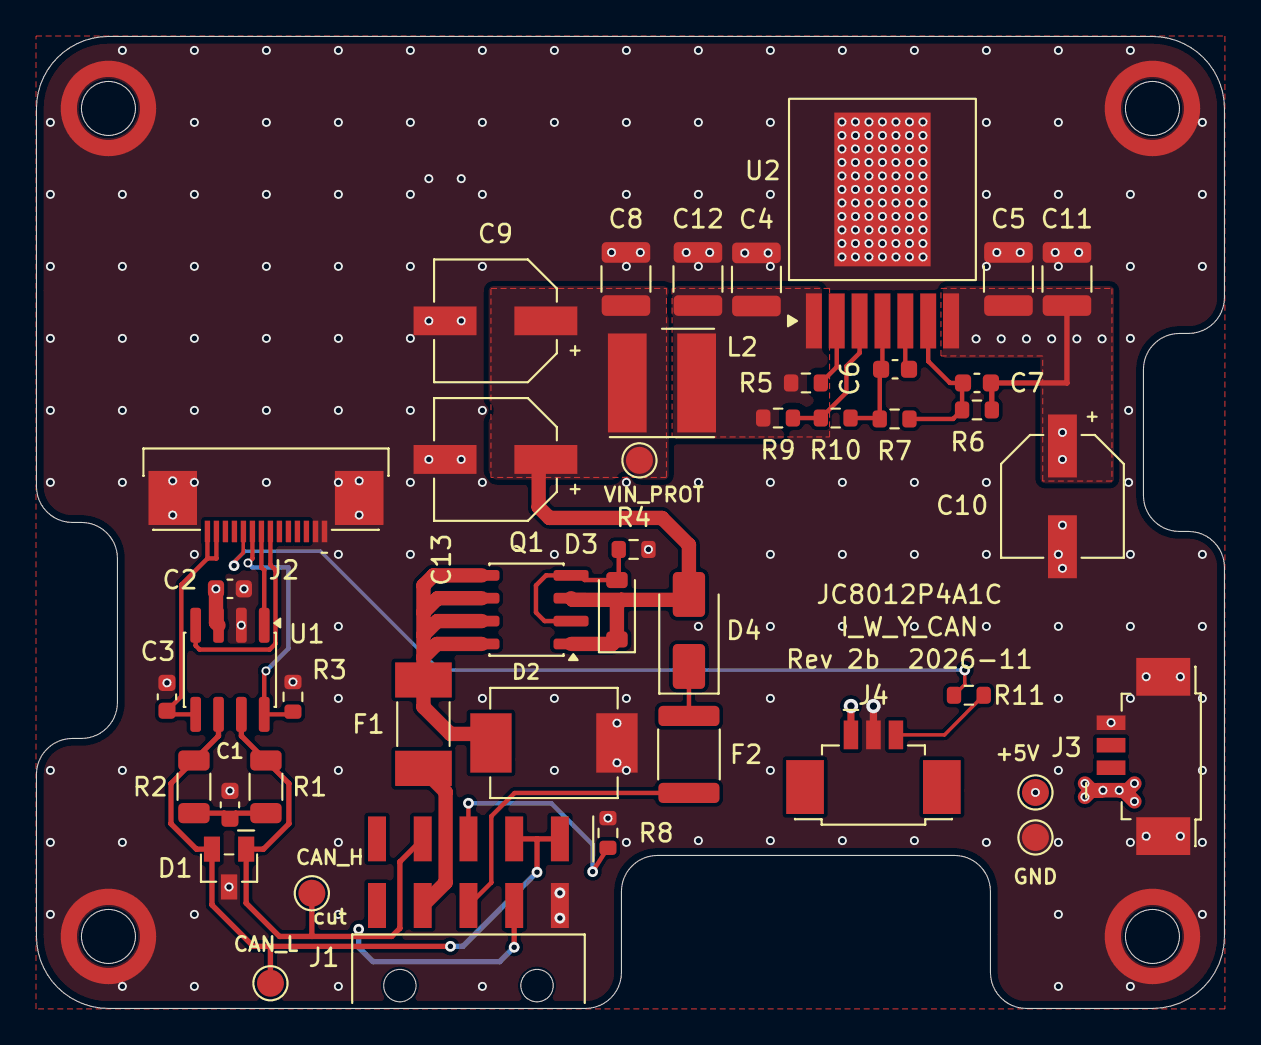
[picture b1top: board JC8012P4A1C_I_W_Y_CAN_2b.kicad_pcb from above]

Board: 6 copper layers, 66.0 x 54.0 mm, 47 parts (0 on the bottom side), 24 nets.

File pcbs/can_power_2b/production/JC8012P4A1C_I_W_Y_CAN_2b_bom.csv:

"Reference","Qty","Value","Manufacturer","MPN","Footprint","DNP"
"C1","1","47n","Wurth Elektronik","885012206093","Capacitor_SMD:C_0603_1608Metric",""
"C2,C3","2","100n","Wurth Elektronik","885012206095","Capacitor_SMD:C_0603_1608Metric",""
"C4,C12","2","10u/50V","Wurth Elektronik","885012209073","Capacitor_SMD:C_1210_3225Metric",""
"C5,C11","2","47u/10V","Wurth Elektronik","885012109007","Capacitor_SMD:C_1210_3225Metric",""
"C6,C7","2","22n","Wurth Elektronik","885012206091","Capacitor_SMD:C_0603_1608Metric",""
"C8","1","1u/50V","Wurth Elektronik","885012209047","Capacitor_SMD:C_1210_3225Metric",""
"C9,C13","2","22u/50V","Wurth Elektronik","865080643008","JC8012P4A1C_CAN:CP_Wurth_WCAP-ASLI-D6.3L5.5",""
"C10","1","220u/10V","Wurth Elektronik","875105244013","JC8012P4A1C_CAN:CP_Wurth_WCAP-PSLP-D6.3L5.8",""
"D1","1","824094024","Wurth Elektronik","824094024","JC8012P4A1C_CAN:D_Wurth_WE-TVS-SOT23-3L",""
"D2","1","824551241","Wurth Elektronik","824551241","JC8012P4A1C_CAN:D_Wurth_WE-TVSP-DO214-AB-3000W_BI",""
"D3","1","15V","Panjit","MMSZ5245B_R1_00001","Diode_SMD:D_SOD-123",""
"D4","1","B160","Diodes Incorporated","B160-13-F","Diode_SMD:D_SMA",""
"F1","1","1A slow 125V","Littelfuse","0452001.MRL","Fuse:Fuse_Littelfuse-NANO2-451_453",""
"F2","1","PTC 0.14A/60V","Bourns","MF-MSMF014-2","Fuse:Fuse_1812_4532Metric",""
"H1-H4","4","Spacer M2 L2.5","Wurth Elektronik","9774025943R","JC8012P4A1C_CAN:A_Wurth_WA-SMST_9774025943R",""
"J1","1","610110249121","Wurth Elektronik","610110249121","JC8012P4A1C_CAN:J_Wurth_WR-PHD_610110249121",""
"J2","1","68711414522","Wurth Elektronik","68711414522","JC8012P4A1C_CAN:J_Wurth_WR-FPC_68711414522",""
"J3","1","653104131822","Wurth Elektronik","653104131822","JC8012P4A1C_CAN:J_Wurth_WR-WTB_653104131822",""
"J4","1","653103131822","Wurth Elektronik","653103131822","JC8012P4A1C_CAN:J_Wurth_WR-WTB_653103131822",""
"L2","1","10uH","Wurth Elektronik","74477410","JC8012P4A1C_CAN:L_Wurth_WE-PD2-5848",""
"Q1","1","Si4948BEY","Vishay","SI4948BEY-T1-E3","Package_SO:SOIC-8_3.9x4.9mm_P1.27mm",""
"R1,R2","2","750 1%","Yageo","RC1206FR-07750RL","Resistor_SMD:R_1206_3216Metric",""
"R3,R10","2","10k 1%","Yageo","RC0603FR-0710KL","Resistor_SMD:R_0603_1608Metric",""
"R4,R5","2","100k 1%","Yageo","RC0603FR-07100KL","Resistor_SMD:R_0603_1608Metric",""
"R6","1","5k62 1%","Yageo","RC0603FR-075K62L","Resistor_SMD:R_0603_1608Metric",""
"R7","1","1k07 1%","Yageo","RC0603FR-071K07L","Resistor_SMD:R_0603_1608Metric",""
"R8","1","0R DNP","Yageo","RC0603JR-070RL","Resistor_SMD:R_0603_1608Metric","Nicht bestücken"
"R9","1","57k6 1%","Yageo","RC0603FR-0757K6L","Resistor_SMD:R_0603_1608Metric",""
"R11","1","33","Yageo","RC0603FR-0733RL","Resistor_SMD:R_0603_1608Metric",""
"U1","1","TLE9250VSJ","Infineon","TLE9250VSJXUMA1","Package_SO:SOIC-8_3.9x4.9mm_P1.27mm",""
"U2","1","171030601","Wurth Elektronik","171030601","JC8012P4A1C_CAN:U_Wurth_WPME-VDRM-TO263-7EP",""

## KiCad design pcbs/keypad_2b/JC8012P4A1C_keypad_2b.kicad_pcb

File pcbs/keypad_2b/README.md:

# JC8012P4A1C keypad, variant 2b (backlit)

The keypad of variant 2 (`../keypad`) with a backlight that the CPU can dim, so the keys
can be found at night without dazzling the driver. KiCad 10 project.

| front (keys, LEDs) | back (J1, J2, level shifter, capacitors) |
|---|---|
|  |  |

Everything that is not mentioned here is the same as in `../keypad/README.md`:
the 3 x 4 key matrix on J1 / FPC4, the sandwich, the mounting in the frame and the screws.

## What is new

- **12 x WL-ICLED 2121** (Würth 1312121320437, RGB with controller, 12 bit PWM + 4 bit
  current per colour) under a white **window** of the foil at the outer top corner of
  every key: left column top left, right column top right (like the windows on the
  Fendt keypads).
- **6 x WL-ICLED side view 3210** (Würth 1313210530000) in pockets of the centre strip
  of the plexiglass. They shine down the strip and light the plexiglass, the grey
  background of the foil glows.
- All 18 LEDs are one chain on one data line: **GPIO2** of the display board
  (FPC3 pin 10), through the CAN board 2b (`../can_power_2b`, R11 33 R, J4) and a
  3 wire cable to **J2** on the keypad. FPC4 has no free pin (the matrix uses all
  7 GPIOs, pins 3-5 are not connected on the display board), so the extra cable is needed.
- **U1 74AHCT1G125** on the keypad lifts the 3.3 V data to 5 V (the ICLEDs need
  V_IH = 0.7 x VDD = 3.5 V). R1 100k pulls the input low, the LEDs stay dark
  while the ESP32-P4 boots or when the cable is unplugged.
- The LEDs run on 5 V from the CAN board (buck converter 5 V / 3 A). The 2121 need
  at least 4.2 V. Idle current about 1 mA per 2121 and 2 mA per side view, about 25 mA in total.
- Colours of the keys: left column F7-F12 **dark green** (Pantone 348 C, about RAL 6002),
  right column F1-F6 **light green** (Pantone 375 C, about RAL 6018).

## Chain and firmware

| LED | index | position |
|---|---|---|
| LED1-LED6 | 0-5 | windows of F7-F12 (left column, top to bottom) |
| LED7-LED12 | 6-11 | windows of F6-F1 (right column, bottom to top) |
| LED13-LED18 | 12-17 | background, side views in the centre strip, top to bottom |

The 2121 take 48 bit per LED (per colour 4 bit current + 12 bit PWM), the side views
24 bit (8 bit per colour, like WS2812). Both use the same bit timing (T0H 0.3 µs,
T1H 0.9 µs, period 1.2 µs). The chain therefore needs its own encoder (RMT) instead of
the stock `led_strip` component: 12 x 48 bit, then 6 x 24 bit, then the reset
(at least 200 µs, the side views need it; the 2121 need 50 µs). Night: current gain 0-1 and PWM a few counts of
4095 for the windows, the side views on 1-3 of 255.
**BI** (bypass input) of the 2121 is tied to GND, the bypass is not used.

## J2 (cable from the CAN board 2b)

Würth WR-WTB 653103131822 (3 pin, 1.25 mm, SMT horizontal) on the back, below J1,
opening towards the left board edge. Cable to J4 of the CAN board 2b, pin n to pin n:

| Pin | Signal |
|---|---|
| 1 | +5V |
| 2 | GND |
| 3 | LED data (GPIO2, 3.3 V) |

Housing 653003113322 on both ends (from the 4 pin housing 653004113322, please check),
pre-crimped wires as for the 5 V cable (pos. 12 of the assembly BOM), length still open.
The cable runs together with the FFC through the cable slot of the frame.

## Plexiglass and foil

Drawing for Folika (1:1, A4) and DXF:
[docs/folika_keypad_12_2b.pdf](docs/folika_keypad_12_2b.pdf),
[docs/folika_keypad_12_2b.dxf](docs/folika_keypad_12_2b.dxf),
made by `docs/make_folika_2b.py` (PyMuPDF + shapely).

Print file for Folika, foil only (no notes): print image with 2 mm bleed and the
cut line as a magenta hairline, 1:1 on a 58 x 160 mm page. Labels and logo are
curves, no fonts and no embedded PDF page, so CorelDraw imports it directly:
[docs/folika_keypad_12_2b_print.svg](docs/folika_keypad_12_2b_print.svg),
[docs/folika_keypad_12_2b_print.pdf](docs/folika_keypad_12_2b_print.pdf).

- Plexiglass (glass clear): additional pocket 3 x 3 mm for every window LED at the outer
  top corner of the key pocket (merged with the diode notch, no thin webs) and
  6 pockets 3.8 x 1.85 mm in the centre strip for the side views.
- Foil: window dia 3 mm, translucent white, centre 8.6 mm beside and 9.6 mm above the key
  centre. Key fields and the grey background printed translucent (no opaque underprint),
  labels black. No adhesive over the windows (dia 4 mm).
- Make a sample first and check how the light spreads and the colours look.

## PCB

48 x 150 mm, 1.6 mm, **4 layers**: F.Cu and B.Cu as in variant 2 (matrix unchanged),
In1.Cu GND plane, In2.Cu +5V plane. LEDs on the front (reflow with the keys),
J2, U1, R1, R2, C1-C20 on the back. The LEDs have no silkscreen (they are under the
plexiglass), see the interactive BOM for the orientation.
ERC, DRC and schematic parity: no errors.

## Parts

[production/JC8012P4A1C_keypad_2b_bom.csv](production/JC8012P4A1C_keypad_2b_bom.csv),
interactive BOM [production/JC8012P4A1C_keypad_2b_ibom.html](production/JC8012P4A1C_keypad_2b_ibom.html).

| Ref | Part |
|---|---|
| S1-S12, D1-D12, H1-H4, J1 | as variant 2 (spacer pads as copper ring 4.2-6.0 mm, 0.25 mm free at the non-plated hole) |
| LED1-LED12 | Würth WL-ICLED 1312121320437 (2121, RGB, 12 bit) |
| LED13-LED18 | Würth WL-ICLED 1313210530000 (side view 3210, RGB) |
| J2 | Würth WR-WTB 653103131822 |
| U1 | TI SN74AHCT1G125DBVR (SOT-23-5) |
| R1 | 100k 0603, R2 33 R 0603 (Yageo) |
| C1 | 10 µF 50 V 1210 Würth 885012209073 |
| C2-C20 | 100 nF 0603 Würth 885012206095 |

## Manufacturing

Gerber and drill files: `production/JC8012P4A1C_keypad_2b_gerber.zip` (4 layers, 1.6 mm).
Two sided assembly: back first (J2 by hand or with its own stencil, U1, R, C), then the
front (keys, diodes, LEDs, spacers) as in variant 2. Commands as for the back plate
(see `../backplate/README.md`) with the project name `JC8012P4A1C_keypad_2b` and the
copper layers `F.Cu,In1.Cu,In2.Cu,B.Cu`.

## Open points

- Check in Fusion that J2 (3.4 mm high) and its plug fit behind the keypad and that the
  3 wire cable fits through the cable slot with the FFC.
- Cable length and housing number (653003113322) from the Würth data sheet.
- Sample of foil and plexiglass: light spread, brightness of the windows, colours.
- Firmware: RMT encoder for the mixed chain (48 bit / 24 bit).

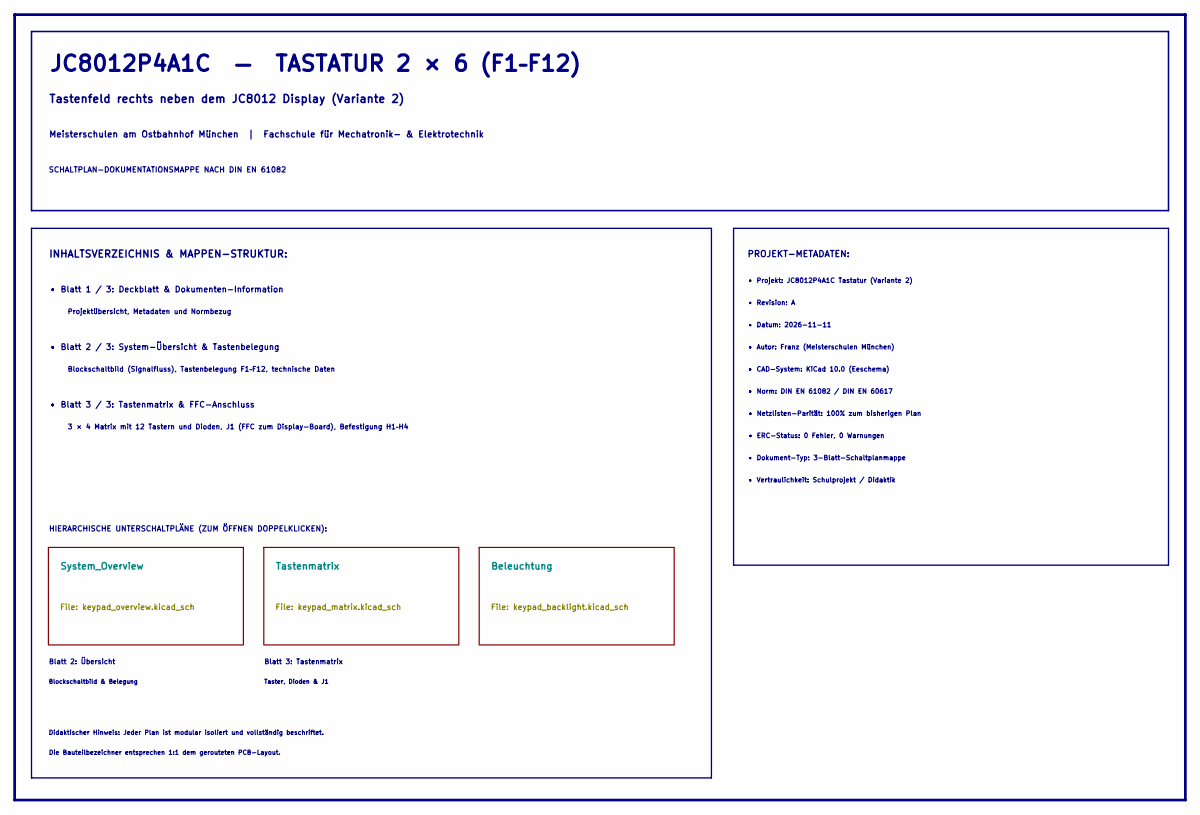
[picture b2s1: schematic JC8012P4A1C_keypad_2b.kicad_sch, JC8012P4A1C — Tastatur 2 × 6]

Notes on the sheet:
SCHALTPLAN-DOKUMENTATIONSMAPPE NACH DIN EN 61082
Projektübersicht, Metadaten und Normbezug
• Norm: DIN EN 61082 / DIN EN 60617
Didaktischer Hinweis: Jeder Plan ist modular isoliert und vollständig beschriftet.
• Blatt 3 / 3: Tastenmatrix & FFC-Anschluss
• Netzlisten-Parität: 100% zum bisherigen Plan
• Datum: 2026-11-11
Blatt 2: Übersicht
Blockschaltbild (Signalfluss), Tastenbelegung F1–F12, technische Daten
JC8012P4A1C — TASTATUR 2 × 6 (F1–F12)
• Revision: A
Blockschaltbild & Belegung
• Vertraulichkeit: Schulprojekt / Didaktik
• CAD-System: KiCad 10.0 (Eeschema)
PROJEKT-METADATEN:
• ERC-Status: 0 Fehler, 0 Warnungen
• Dokument-Typ: 3-Blatt-Schaltplanmappe
Tastenfeld rechts neben dem JC8012 Display (Variante 2)
• Projekt: JC8012P4A1C Tastatur (Variante 2)
• Autor: Franz (Meisterschulen München)
• Blatt 1 / 3: Deckblatt & Dokumenten-Information
Die Bauteilbezeichner entsprechen 1:1 dem gerouteten PCB-Layout.
• Blatt 2 / 3: System-Übersicht & Tastenbelegung
Blatt 3: Tastenmatrix
Meisterschulen am Ostbahnhof München | Fachschule für Mechatronik- & Elektrotechnik
HIERARCHISCHE UNTERSCHALTPLÄNE (ZUM ÖFFNEN DOPPELKLICKEN):
INHALTSVERZEICHNIS & MAPPEN-STRUKTUR:
3 × 4 Matrix mit 12 Tastern und Dioden, J1 (FFC zum Display-Board), Befestigung H1–H4
Taster, Dioden & J1
